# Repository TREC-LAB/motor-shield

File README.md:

# PCB Motor Controller Shield V1.1

## Getting started

To make it easy for you to get started with GitLab, here's a list of recommended next steps.

Already a pro? Just edit this README.md and make it your own. Want to make it easy? [Use the template at the bottom](#editing-this-readme)!

## Add your files

- [ ] [Create](https://docs.gitlab.com/ee/user/project/repository/web_editor.html#create-a-file) or [upload](https://docs.gitlab.com/ee/user/project/repository/web_editor.html#upload-a-file) files
- [ ] [Add files using the command line](https://docs.gitlab.com/ee/gitlab-basics/add-file.html#add-a-file-using-the-command-line) or push an existing Git repository with the following command:

```
cd existing_repo
git remote add origin http://192.168.1.88/trec-lab/pandora-low-level-design/pcb-motor-controller-shield-v1.1.git
git branch -M main
git push -uf origin main
```

## Integrate with your tools

- [ ] [Set up project integrations](http://192.168.1.88/trec-lab/pandora-low-level-design/pcb-motor-controller-shield-v1.1/-/settings/integrations)

## Collaborate with your team

- [ ] [Invite team members and collaborators](https://docs.gitlab.com/ee/user/project/members/)
- [ ] [Create a new merge request](https://docs.gitlab.com/ee/user/project/merge_requests/creating_merge_requests.html)
- [ ] [Automatically close issues from merge requests](https://docs.gitlab.com/ee/user/project/issues/managing_issues.html#closing-issues-automatically)
- [ ] [Enable merge request approvals](https://docs.gitlab.com/ee/user/project/merge_requests/approvals/)
- [ ] [Automatically merge when pipeline succeeds](https://docs.gitlab.com/ee/user/project/merge_requests/merge_when_pipeline_succeeds.html)

## Test and Deploy

Use the built-in continuous integration in GitLab.

- [ ] [Get started with GitLab CI/CD](https://docs.gitlab.com/ee/ci/quick_start/index.html)
- [ ] [Analyze your code for known vulnerabilities with Static Application Security Testing(SAST)](https://docs.gitlab.com/ee/user/application_security/sast/)
- [ ] [Deploy to Kubernetes, Amazon EC2, or Amazon ECS using Auto Deploy](https://docs.gitlab.com/ee/topics/autodevops/requirements.html)
- [ ] [Use pull-based deployments for improved Kubernetes management](https://docs.gitlab.com/ee/user/clusters/agent/)
- [ ] [Set up protected environments](https://docs.gitlab.com/ee/ci/environments/protected_environments.html)

***

# Editing this README

When you're ready to make this README your own, just edit this file and use the handy template below (or feel free to structure it however you want - this is just a starting point!). Thank you to [makeareadme.com](https://www.makeareadme.com/) for this template.

## Suggestions for a good README
Every project is different, so consider which of these sections apply to yours. The sections used in the template are suggestions for most open source projects. Also keep in mind that while a README can be too long and detailed, too long is better than too short. If you think your README is too long, consider utilizing another form of documentation rather than cutting out information.

## Name
Choose a self-explaining name for your project.

## Description
Let people know what your project can do specifically. Provide context and add a link to any reference visitors might be unfamiliar with. A list of Features or a Background subsection can also be added here. If there are alternatives to your project, this is a good place to list differentiating factors.

## Badges
On some READMEs, you may see small images that convey metadata, such as whether or not all the tests are passing for the project. You can use Shields to add some to your README. Many services also have instructions for adding a badge.

## Visuals
Depending on what you are making, it can be a good idea to include screenshots or even a video (you'll frequently see GIFs rather than actual videos). Tools like ttygif can help, but check out Asciinema for a more sophisticated method.

## Installation
Within a particular ecosystem, there may be a common way of installing things, such as using Yarn, NuGet, or Homebrew. However, consider the possibility that whoever is reading your README is a novice and would like more guidance. Listing specific steps helps remove ambiguity and gets people to using your project as quickly as possible. If it only runs in a specific context like a particular programming language version or operating system or has dependencies that have to be installed manually, also add a Requirements subsection.

## Usage
Use examples liberally, and show the expected output if you can. It's helpful to have inline the smallest example of usage that you can demonstrate, while providing links to more sophisticated examples if they are too long to reasonably include in the README.

## Support
Tell people where they can go to for help. It can be any combination of an issue tracker, a chat room, an email address, etc.

## Roadmap
If you have ideas for releases in the future, it is a good idea to list them in the README.

## Contributing
State if you are open to contributions and what your requirements are for accepting them.

For people who want to make changes to your project, it's helpful to have some documentation on how to get started. Perhaps there is a script that they should run or some environment variables that they need to set. Make these steps explicit. These instructions could also be useful to your future self.

You can also document commands to lint the code or run tests. These steps help to ensure high code quality and reduce the likelihood that the changes inadvertently break something. Having instructions for running tests is especially helpful if it requires external setup, such as starting a Selenium server for testing in a browser.

## Authors and acknowledgment
Show your appreciation to those who have contributed to the project.

## License
For open source projects, say how it is licensed.

## Project status
If you have run out of energy or time for your project, put a note at the top of the README saying that development has slowed down or stopped completely. Someone may choose to fork your project or volunteer to step in as a maintainer or owner, allowing your project to keep going. You can also make an explicit request for maintainers.

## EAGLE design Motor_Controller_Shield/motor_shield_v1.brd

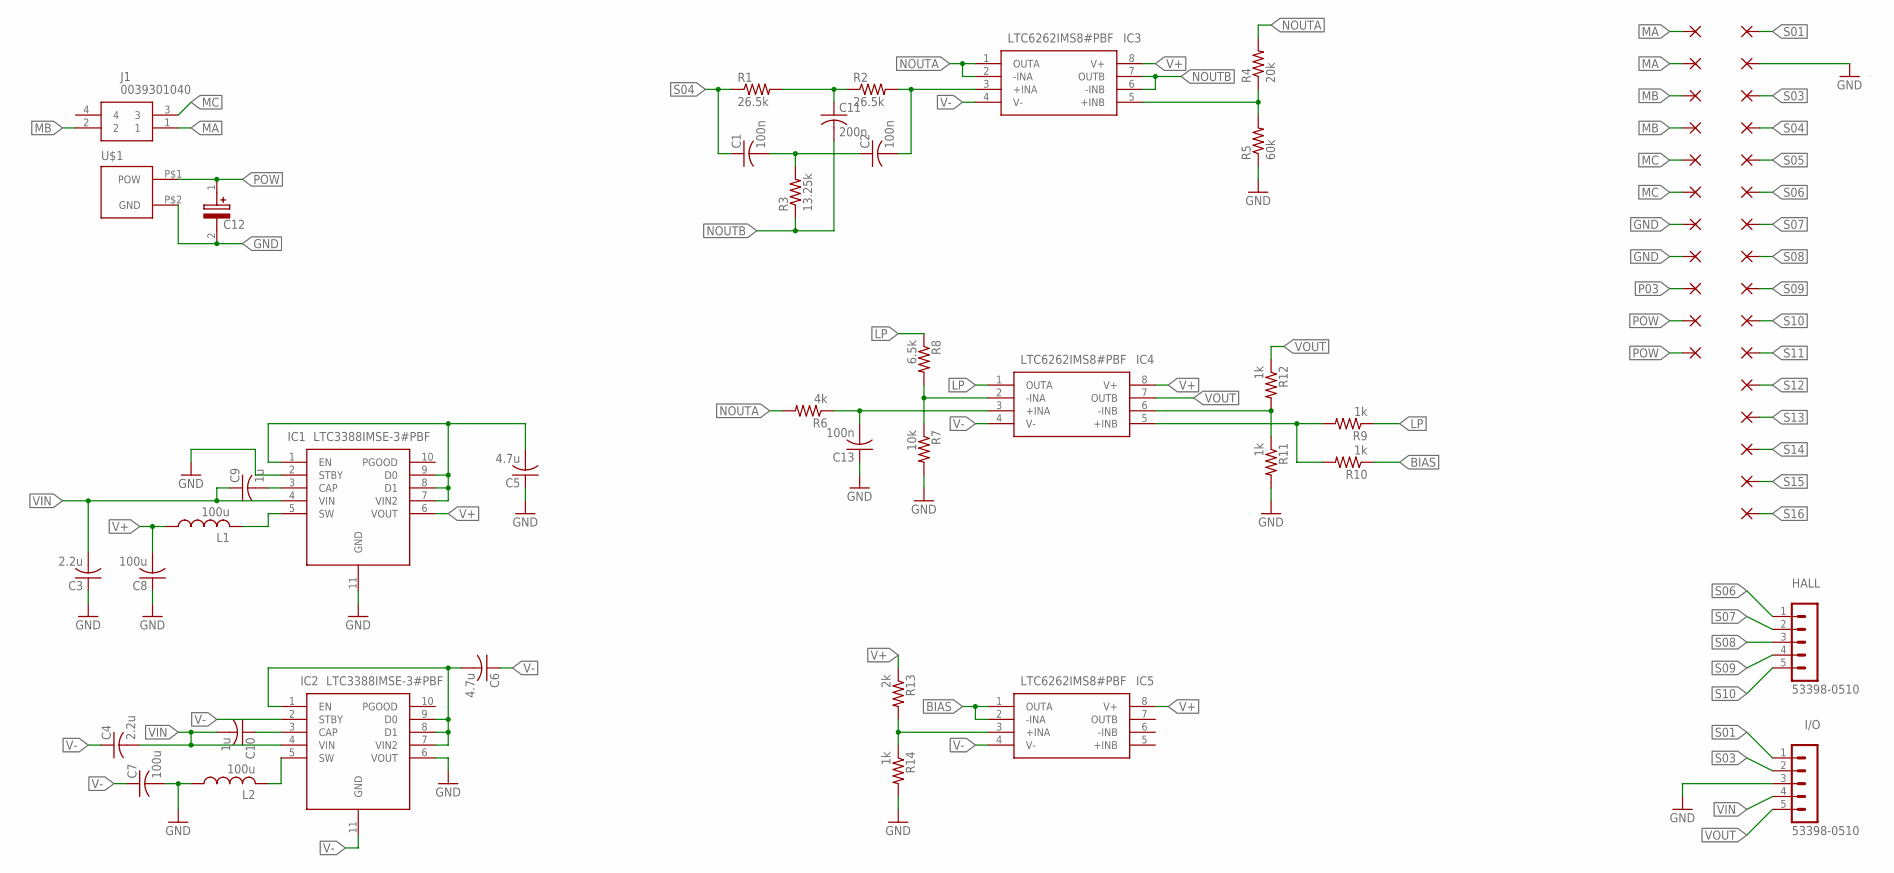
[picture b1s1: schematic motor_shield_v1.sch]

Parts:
C1, C2, C13: 100n; C0805
C3, C4: 2.2u; C0805
C5, C6: 4.7u; C0805
C7, C8: 100u; C0805
C9, C10: 1u; C0805
C11: 200n; C0805
C12: UVR2A101MPD; CAPPRD500W60D1025H2200
HALL: 53398-0510
I/O: 53398-0510
IC1, IC2: LTC3388IMSE-3#PBF; SOP50P490X110-11N
IC3, IC4, IC5: LTC6262IMS8#PBF; SOP65P490X110-8N
J1: 0039301040
L1, L2: 100u; L2012C
P01, P02, P03, P04, P05, P06, P07, P08, P09, P10, P11: 1,6/0,9
R1, R2: 26.5k; R0805
R3: 13.25k; R0805
R4: 20k; R0805
R5: 60k; R0805
R6: 4k; R0805
R7: 10k; R0805
R8: 6.5k; R0805
R9, R10, R11, R12, R14: 1k; R0805
R13: 2k; R0805
S01, S02, S03, S04, S05, S06, S07, S08, S09, S10, S11, S12, S13, S14, S15, S16: 1,6/0,9
U$1: JR_2PM_DEV; JR_2PM_B_FP

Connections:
BIAS: IC5.1 (OUTA), IC5.2 (-INA), R10.1
GND: C3.1, C5.1, C7.2, C8.1, C12.2 (-), C13.1, I/O.3, IC1.2 (STBY), IC1.11 (GND), IC2.6 (VOUT), L2.1, P07.1, P08.1, R5.1, R7.2, R11.2, R14.2, S02.1, U$1.P$2 (GND)
LP: IC4.1 (OUTA), R8.1, R9.1
MA: J1.1, P01.1, P02.1
MB: J1.2, P03.1, P04.1
MC: J1.3, P05.1, P06.1
unnamed: IC2.5 (SW), L2.2
unnamed: IC3.5 (+INB), R4.1, R5.2
unnamed: C2.2, IC3.3 (+INA), R2.2
unnamed: C13.2, IC4.3 (+INA), R6.1
unnamed: C11.1, R1.2, R2.1
unnamed: C6.2, IC2.1 (EN), IC2.7 (VIN2), IC2.8 (D1), IC2.9 (D0)
unnamed: C1.2, C2.1, R3.2
unnamed: IC4.2 (-INA), R7.1, R8.2
unnamed: C10.1, IC2.3 (CAP)
unnamed: IC5.3 (+INA), R13.2, R14.1
unnamed: IC4.6 (-INB), R11.1, R12.2
unnamed: IC4.5 (+INB), R9.2, R10.2
unnamed: C5.2, IC1.1 (EN), IC1.7 (VIN2), IC1.8 (D1), IC1.9 (D0)
unnamed: C9.2, IC1.3 (CAP)
unnamed: IC1.5 (SW), L1.2
NOUTA: IC3.1 (OUTA), IC3.2 (-INA), R4.2, R6.2
NOUTB: C11.2, IC3.6 (-INB), IC3.7 (OUTB), R3.1
P03: P09.1
POW: C12.1 (+), P10.1, P11.1, U$1.P$1 (POW)
S01: I/O.1, S01.1
S03: I/O.2, S03.1
S04: C1.1, R1.1, S04.1
S05: S05.1
S06: HALL.1, S06.1
S07: HALL.2, S07.1
S08: HALL.3, S08.1
S09: HALL.4, S09.1
S10: HALL.5, S10.1
S11: S11.1
S12: S12.1
S13: S13.1
S14: S14.1
S15: S15.1
S16: S16.1
V+: C8.2, IC1.6 (VOUT), IC3.8 (V+), IC4.8 (V+), IC5.8 (V+), L1.1, R13.1
V-: C4.1, C6.1, C7.1, IC2.2 (STBY), IC2.11 (GND), IC3.4 (V-), IC4.4 (V-), IC5.4 (V-)
VIN: C3.2, C4.2, C9.1, C10.2, I/O.4, IC1.4 (VIN), IC2.4 (VIN)
VOUT: I/O.5, IC4.7 (OUTB), R12.1

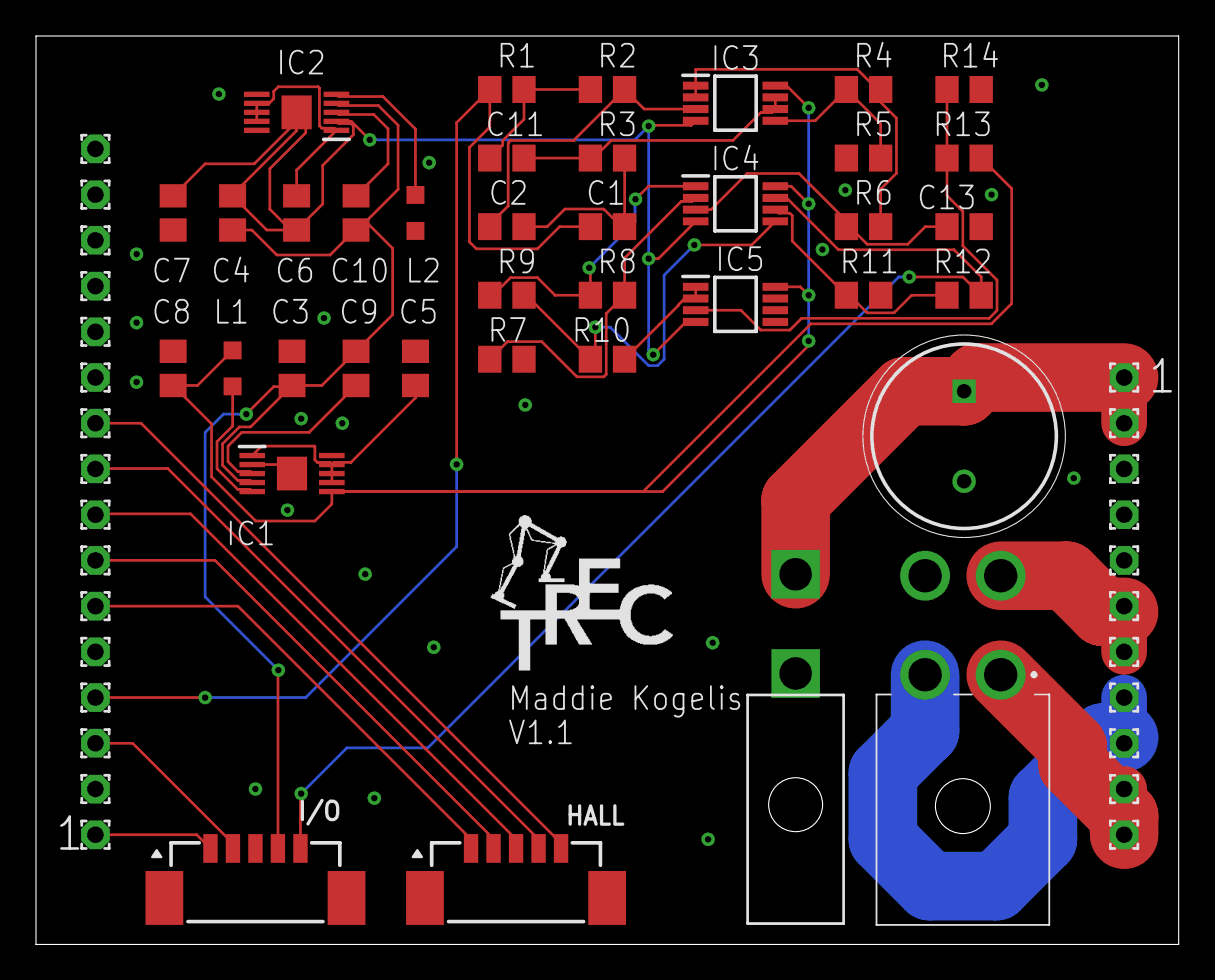
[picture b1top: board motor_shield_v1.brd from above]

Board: 2 copper layers, 63.5 x 50.5 mm, 65 parts (0 on the bottom side), 36 nets.

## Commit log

2022-12-03 What I have of Motor Controller Shield V1.1
    Ask Maddie to delete and update it with her most recent file.
    -Zach

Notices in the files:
parts and their libraries:
con-molex-picoblade: Copyright (C) 2010, Bob Starr
